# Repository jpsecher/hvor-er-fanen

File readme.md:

# Alien & Ko Tracker

There are two projects in this repo:
- PCB for the tracking device and its enclosure (`ak-tracker/` and `enclosure.FCStd`), described in [ak-tracker/readme.md](./ak-tracker/readme.md).
- RGB Matrix display (`dev/`), wired as described in [doc/rgb-matrix-wiring.md](./doc/rgb-matrix-wiring.md), built and flashed as described in [doc/rgb-matrix-development.md](./doc/rgb-matrix-development.md).

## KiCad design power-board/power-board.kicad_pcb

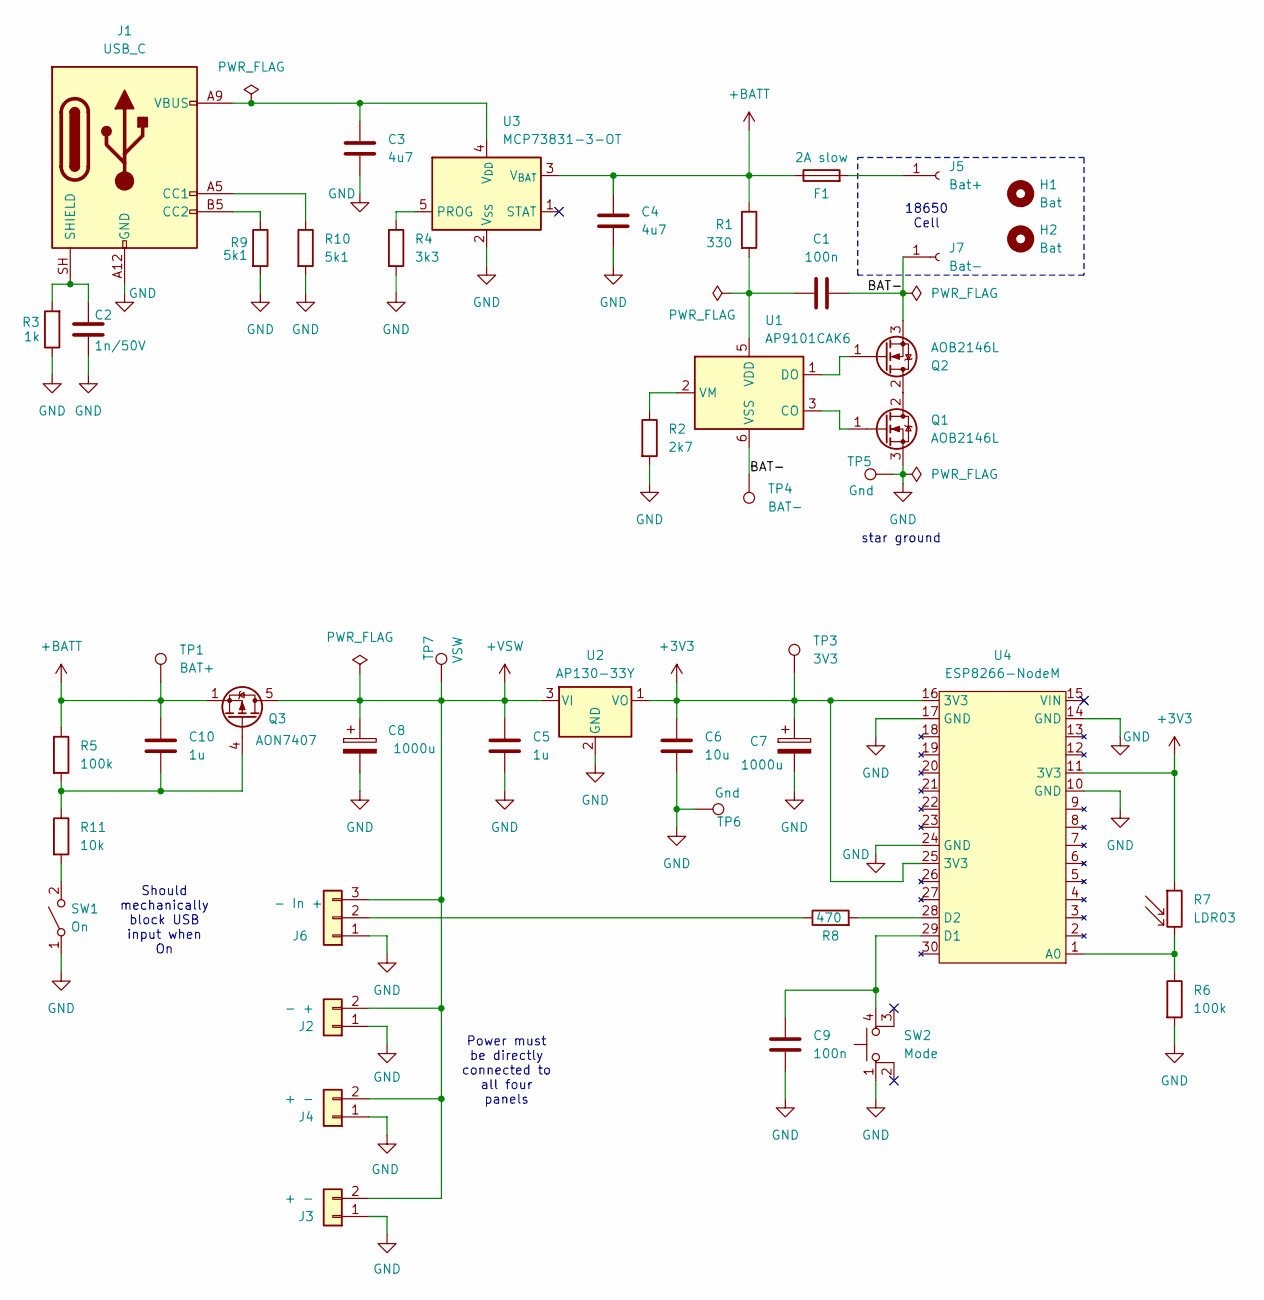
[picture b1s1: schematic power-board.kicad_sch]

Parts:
C1, C9: 100n; C_0805_2012Metric_Pad1.18x1.45mm_HandSolder
C2: 1n/50V; C_0805_2012Metric_Pad1.18x1.45mm_HandSolder
C3, C4: 4u7; C_0805_2012Metric_Pad1.18x1.45mm_HandSolder
C5, C10: 1u; C_0805_2012Metric_Pad1.18x1.45mm_HandSolder
C6: 10u; C_0805_2012Metric_Pad1.18x1.45mm_HandSolder
C7, C8: 1000u; CP_Radial_D10.0mm_P5.00mm
F1: 2A slow; Fuseholder_Cylinder-5x20mm_Schurter_0031_8201_Horizontal_Op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
H1, H2: Bat; MountingHole_3.2mm_M3
J1: USB_C; USB_C_Receptacle_GCT_USB4125-xx-x-0190_6P_TopMnt_Horizontal
J2: - +; PinHeader_2x01_P2.54mm_Vertical
J3, J4: + -; PinHeader_2x01_P2.54mm_Vertical
J5: Bat+; Pin_D1.3mm_L11.0mm_LooseFit
J6: - In +; PinHeader_1x03_P2.54mm_Vertical
J7: Bat-; Pin_D1.3mm_L11.0mm_LooseFit
Q1, Q2: AOB2146L; TO-263-2
Q3: AON7407; AO_DFN-8-1EP_5.55x5.2mm_P1.27mm_EP4.12x4.6mm
R1: 330; R_0805_2012Metric_Pad1.20x1.40mm_HandSolder
R2: 2k7; R_0805_2012Metric_Pad1.20x1.40mm_HandSolder
R3: 1k; R_0805_2012Metric_Pad1.20x1.40mm_HandSolder
R4: 3k3; R_0805_2012Metric_Pad1.20x1.40mm_HandSolder
R5, R6: 100k; R_0805_2012Metric_Pad1.20x1.40mm_HandSolder
R7: LDR03; R_LDR_10x8.5mm_P7.6mm_Vertical
R8: 470; R_0805_2012Metric_Pad1.20x1.40mm_HandSolder
R9, R10: 5k1; R_0805_2012Metric_Pad1.20x1.40mm_HandSolder
R11: 10k; R_0805_2012Metric_Pad1.20x1.40mm_HandSolder
SW1: On; PinHeader_2x01_P2.54mm_Vertical
SW2: Mode; SW_Push_2P1T_Toggle_CK_PVA1xxH1xxxxxxV2
TP1: BAT+; TestPoint_Pad_2.0x2.0mm
TP3: 3V3; TestPoint_Pad_2.0x2.0mm
TP4: BAT-; TestPoint_Pad_2.0x2.0mm
TP5, TP6: Gnd; TestPoint_Pad_2.0x2.0mm
TP7: VSW; TestPoint_Pad_2.0x2.0mm
U1: AP9101CAK6; SOT-23-6
U2: AP130-33Y; SOT-89-3
U3: MCP73831-3-OT; SOT-23-5
U4: ESP8266-NodeM; ESP32-C3-DevKitM-1

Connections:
+3V3: C6.1, C7.1, R7.1, TP3.1 (1_1), U2.1 (VO), U4.11 (3V3), U4.16 (3V3), U4.25 (3V3)
+BATT: C4.1, C10.1, F1.1, Q3.1 (S), Q3.2 (S), Q3.3 (S), R1.1, R5.1, TP1.1 (1_1), U3.3 (V_{BAT})
+VSW: C5.1, C8.1, J2.2, J3.2, J4.2, J6.3, Q3.5 (D), TP7.1 (1_1), U2.3 (VI)
/BAT-: C1.2, J7.1 (Pin_1_1), Q2.3 (S), TP4.1 (1_1), U1.6 (VSS)
GND: C2.2, C3.2, C4.2, C5.2, C6.2, C7.2, C8.2, C9.1, J1.A12 (GND), J1.B12 (GND), J2.1, J3.1, J4.1, J6.1, Q1.3 (S), R2.2, R3.1, R4.2, R6.2, R9.2, R10.2, SW1.1 (A), SW2.1, TP5.1 (1_1), TP6.1 (1_1), U2.2 (GND), U3.2 (V_{SS}), U4.10 (GND), U4.14 (GND), U4.17 (GND), U4.24 (GND)
unnamed: J1.A5 (CC1), R10.1
unnamed: J1.B5 (CC2), R9.1
unnamed: C2.1, J1.SH (SHIELD), R3.2
unnamed: F1.2, J5.1 (Pin_1_1)
unnamed: J6.2, R8.1
unnamed: Q1.2 (D), Q2.2 (D)
unnamed: Q1.1 (G), U1.3 (CO)
unnamed: Q2.1 (G), U1.1 (DO)
unnamed: C10.2, Q3.4 (G), R5.2, R11.1
unnamed: R11.2, SW1.2 (B)
unnamed: C9.2, SW2.4 (A), U4.29 (D1)
unnamed: C1.1, R1.2, U1.5 (VDD)
unnamed: R2.1, U1.2 (VM)
unnamed: R4.1, U3.5 (PROG)
unnamed: C3.1, J1.A9 (VBUS), J1.B9 (VBUS), U3.4 (V_{DD})
unnamed: R6.1, R7.2, U4.1 (A0)
unnamed: R8.2, U4.28 (D2)

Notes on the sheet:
Power must be directly connected to all four panels
Should mechanically block USB input when On
star ground
18650 Cell

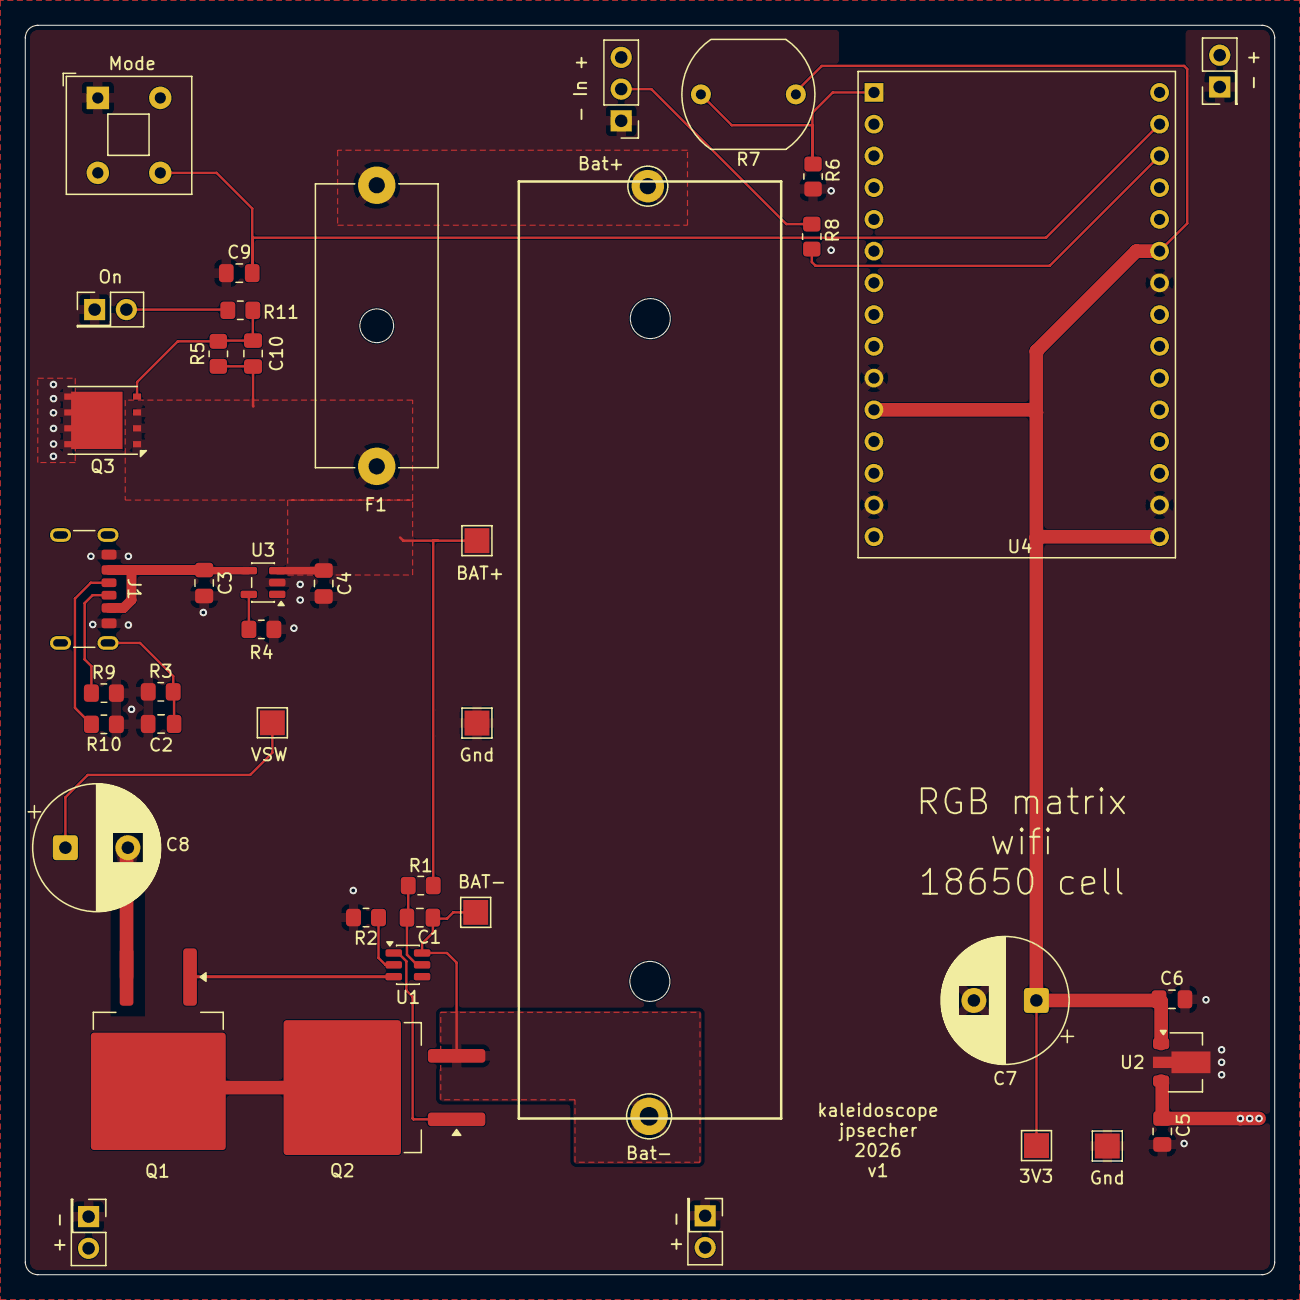
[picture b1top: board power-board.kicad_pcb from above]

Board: 2 copper layers, 100.0 x 100.0 mm, 46 parts (0 on the bottom side), 22 nets.

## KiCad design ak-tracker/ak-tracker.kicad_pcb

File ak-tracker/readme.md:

# Hat for Alien & Ko Tracker

Add-on board for Helltec CubeCell HTCC-AB02S.

- Must provide movement data to HTCC-AB02S
- Must serve as Watchdog for HTCC-AB02S
- Must take up as little room as possible

## References

- [Helltec AB02S diagram](./doc/HTCC-AB02S_SchematicDiagram_V1.1.pdf), [Helltec AB02S pinout](./doc/HTCC-AB02S-pinout.png), [original](https://resource.heltec.cn/download/CubeCell/HTCC-AB02S/HTCC-AB02S_SchematicDiagram_V1.1.pdf)
- [Bosch BMA400](./doc/bst-bma400-ds000.pdf), [original](https://www.bosch-sensortec.com/en/products/motion-sensors/accelerometers/bma400)
- [TI TPL5010](./doc/tpl5010.pdf)

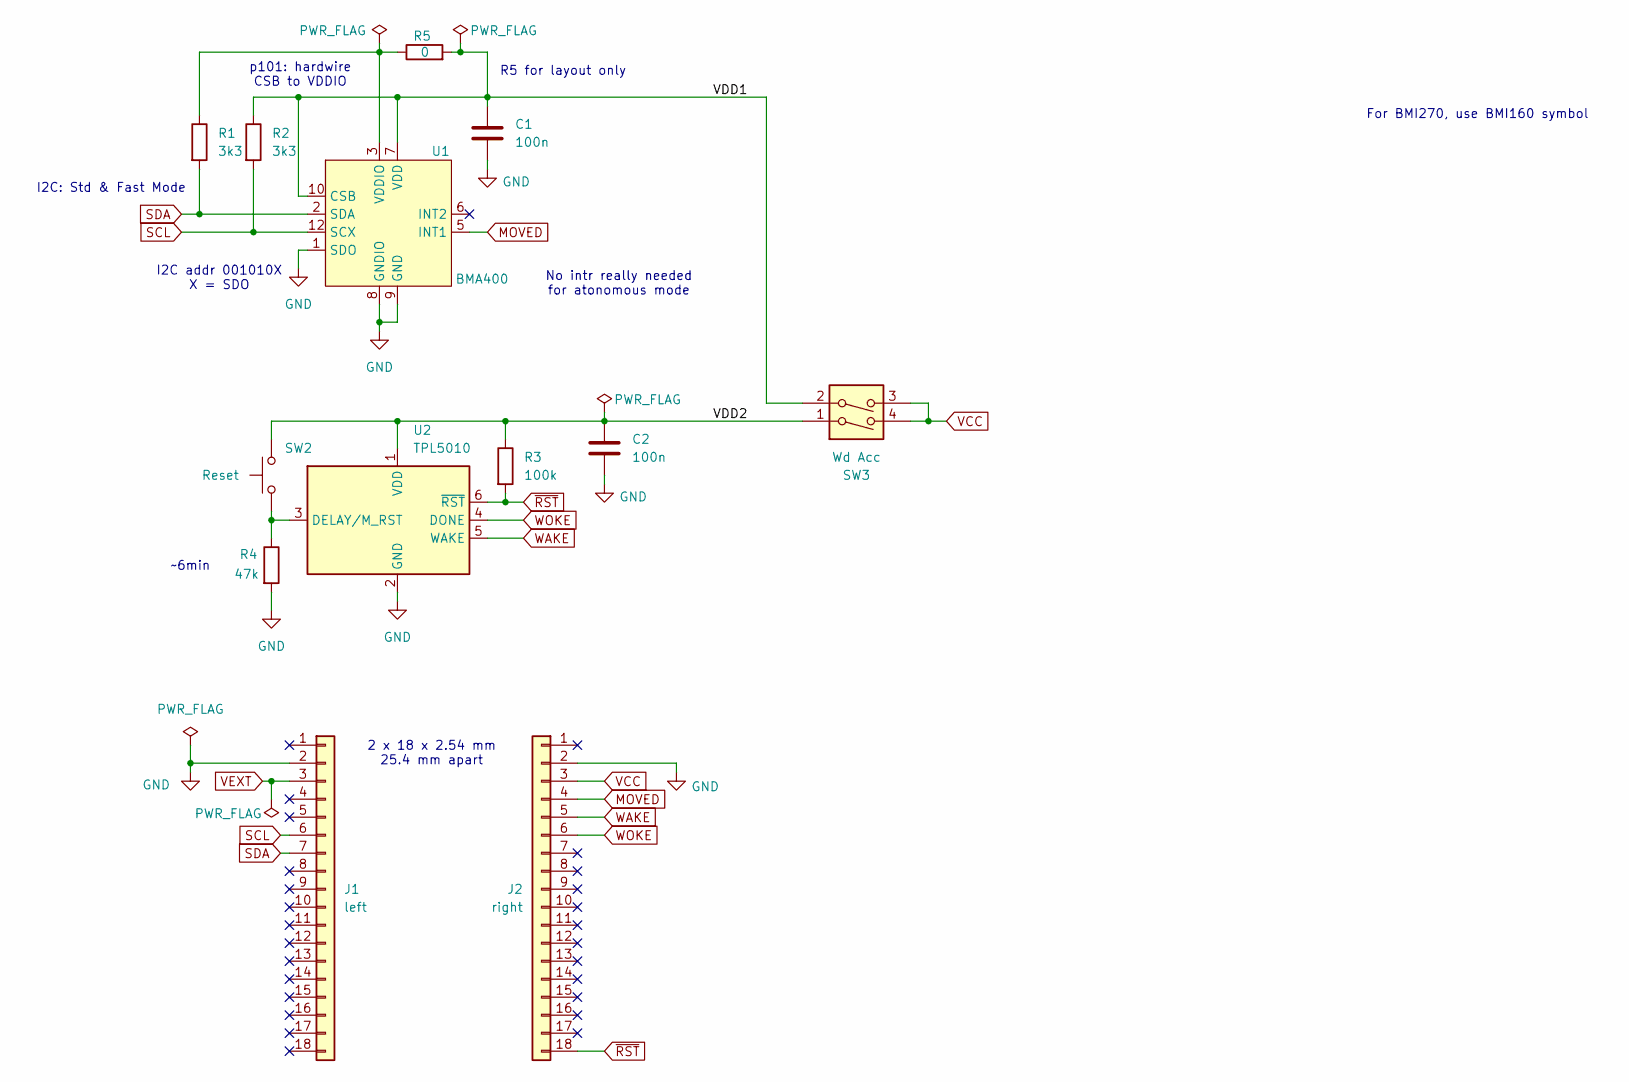
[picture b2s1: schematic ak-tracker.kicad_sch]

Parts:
C1, C2: 100n; C_0805_2012Metric_Pad1.18x1.45mm_HandSolder
J1: left; PinHeader_1x18_P2.54mm_Vertical
J2: right; PinHeader_1x18_P2.54mm_Vertical
R1, R2: 3k3; R_0805_2012Metric_Pad1.20x1.40mm_HandSolder
R3: 100k; R_0805_2012Metric_Pad1.20x1.40mm_HandSolder
R4: 47k; R_0805_2012Metric_Pad1.20x1.40mm_HandSolder
R5: 0; R_0805_2012Metric_Pad1.20x1.40mm_HandSolder
SW2: Reset; SW_Push_1P1T_NO_CK_KSC9xxG
SW3: Wd Acc; SW_DIP_SPSTx02_Slide_9.78x7.26mm_W8.61mm_P2.54mm
U1: BMA400; LGA-12_2x2mm_P0.5mm
U2: TPL5010; SOT-23-6

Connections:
/VDD1: C1.1, R2.1, R5.2, SW3.2, U1.7 (VDD), U1.10 (CSB)
/VDD2: C2.1, R3.1, SW2.2, SW3.1, U2.1 (VDD)
GND: C1.2, C2.2, J1.2, J2.2, R4.2, U1.1 (SDO), U1.8 (GNDIO), U1.9 (GND), U2.2 (GND)
MOVED: J2.4, U1.5 (INT1)
unnamed: R1.1, R5.1, U1.3 (VDDIO)
unnamed: R4.1, SW2.1, U2.3 (DELAY/M_RST)
SCL: J1.6, R2.2, U1.12 (SCX)
SDA: J1.7, R1.2, U1.2 (SDA)
VCC: J2.3, SW3.3, SW3.4
VEXT: J1.3
WAKE: J2.5, U2.5 (WAKE)
WOKE: J2.6, U2.4 (DONE)
~RST: J2.18, R3.2, U2.6 (~RST)

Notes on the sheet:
For BMI270, use BMI160 symbol
2 x 18 x 2.54 mm 25.4 mm apart
p101: hardwire CSB to VDDIO
~6min
R5 for layout only
I2C: Std & Fast Mode
No intr really needed for atonomous mode
I2C addr 001010X X = SDO

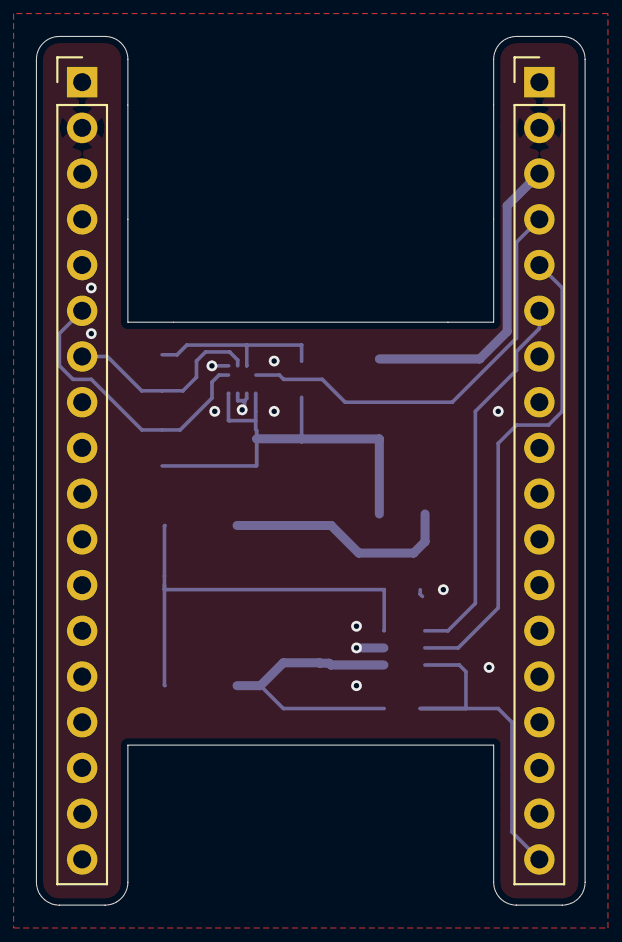
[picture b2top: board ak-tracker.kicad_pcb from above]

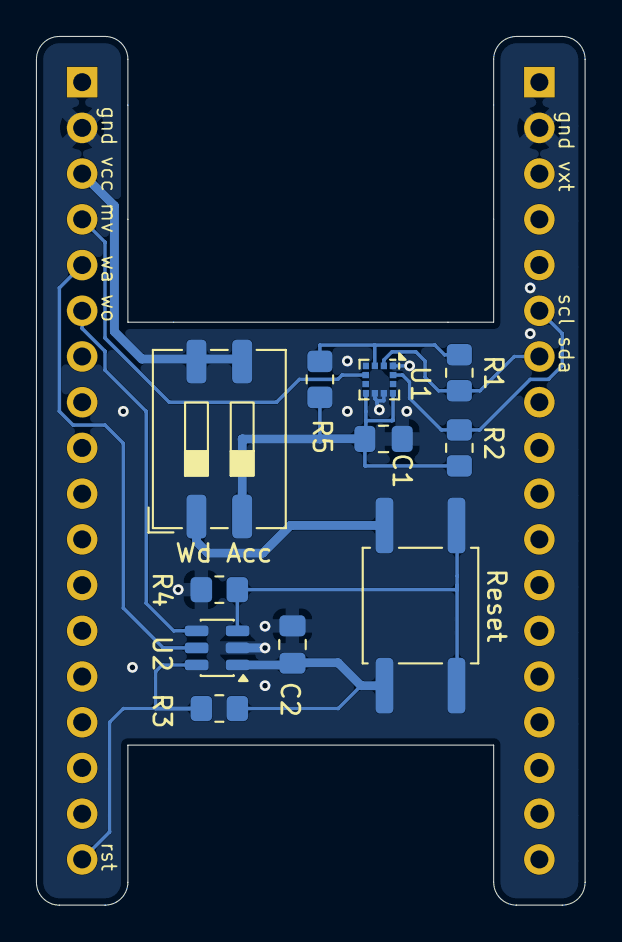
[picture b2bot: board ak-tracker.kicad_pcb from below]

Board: 2 copper layers, 30.5 x 48.3 mm, 13 parts (11 on the bottom side), 12 nets.

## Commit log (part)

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2026-04-02 init
2026-04-02 BMA400 symbol
2026-04-13 docs
2026-04-14 TPL5010 and BMA400 as symbols in KiCad
2026-04-14 Helltec AB02S diagram
2026-04-14 better layout of BMA400
2026-04-14 initial schematic
2026-04-15 footprints
2026-04-16 initial routing
2026-04-16 better routing
2026-04-17 interrupts to 5,6,7
2026-04-26 smaller i2c pullup
2026-04-26 3k3 & silk screen
2026-05-16 base shape of enclosure
2026-05-16 rounded corners
2026-05-16 lip on main body
2026-05-17 enclosure v1
